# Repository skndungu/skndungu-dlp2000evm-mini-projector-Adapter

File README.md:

# skndungu-dlp2000evm-mini-projector-Adapter
dlp2000evm mini projector Raspberry Pi Adapter

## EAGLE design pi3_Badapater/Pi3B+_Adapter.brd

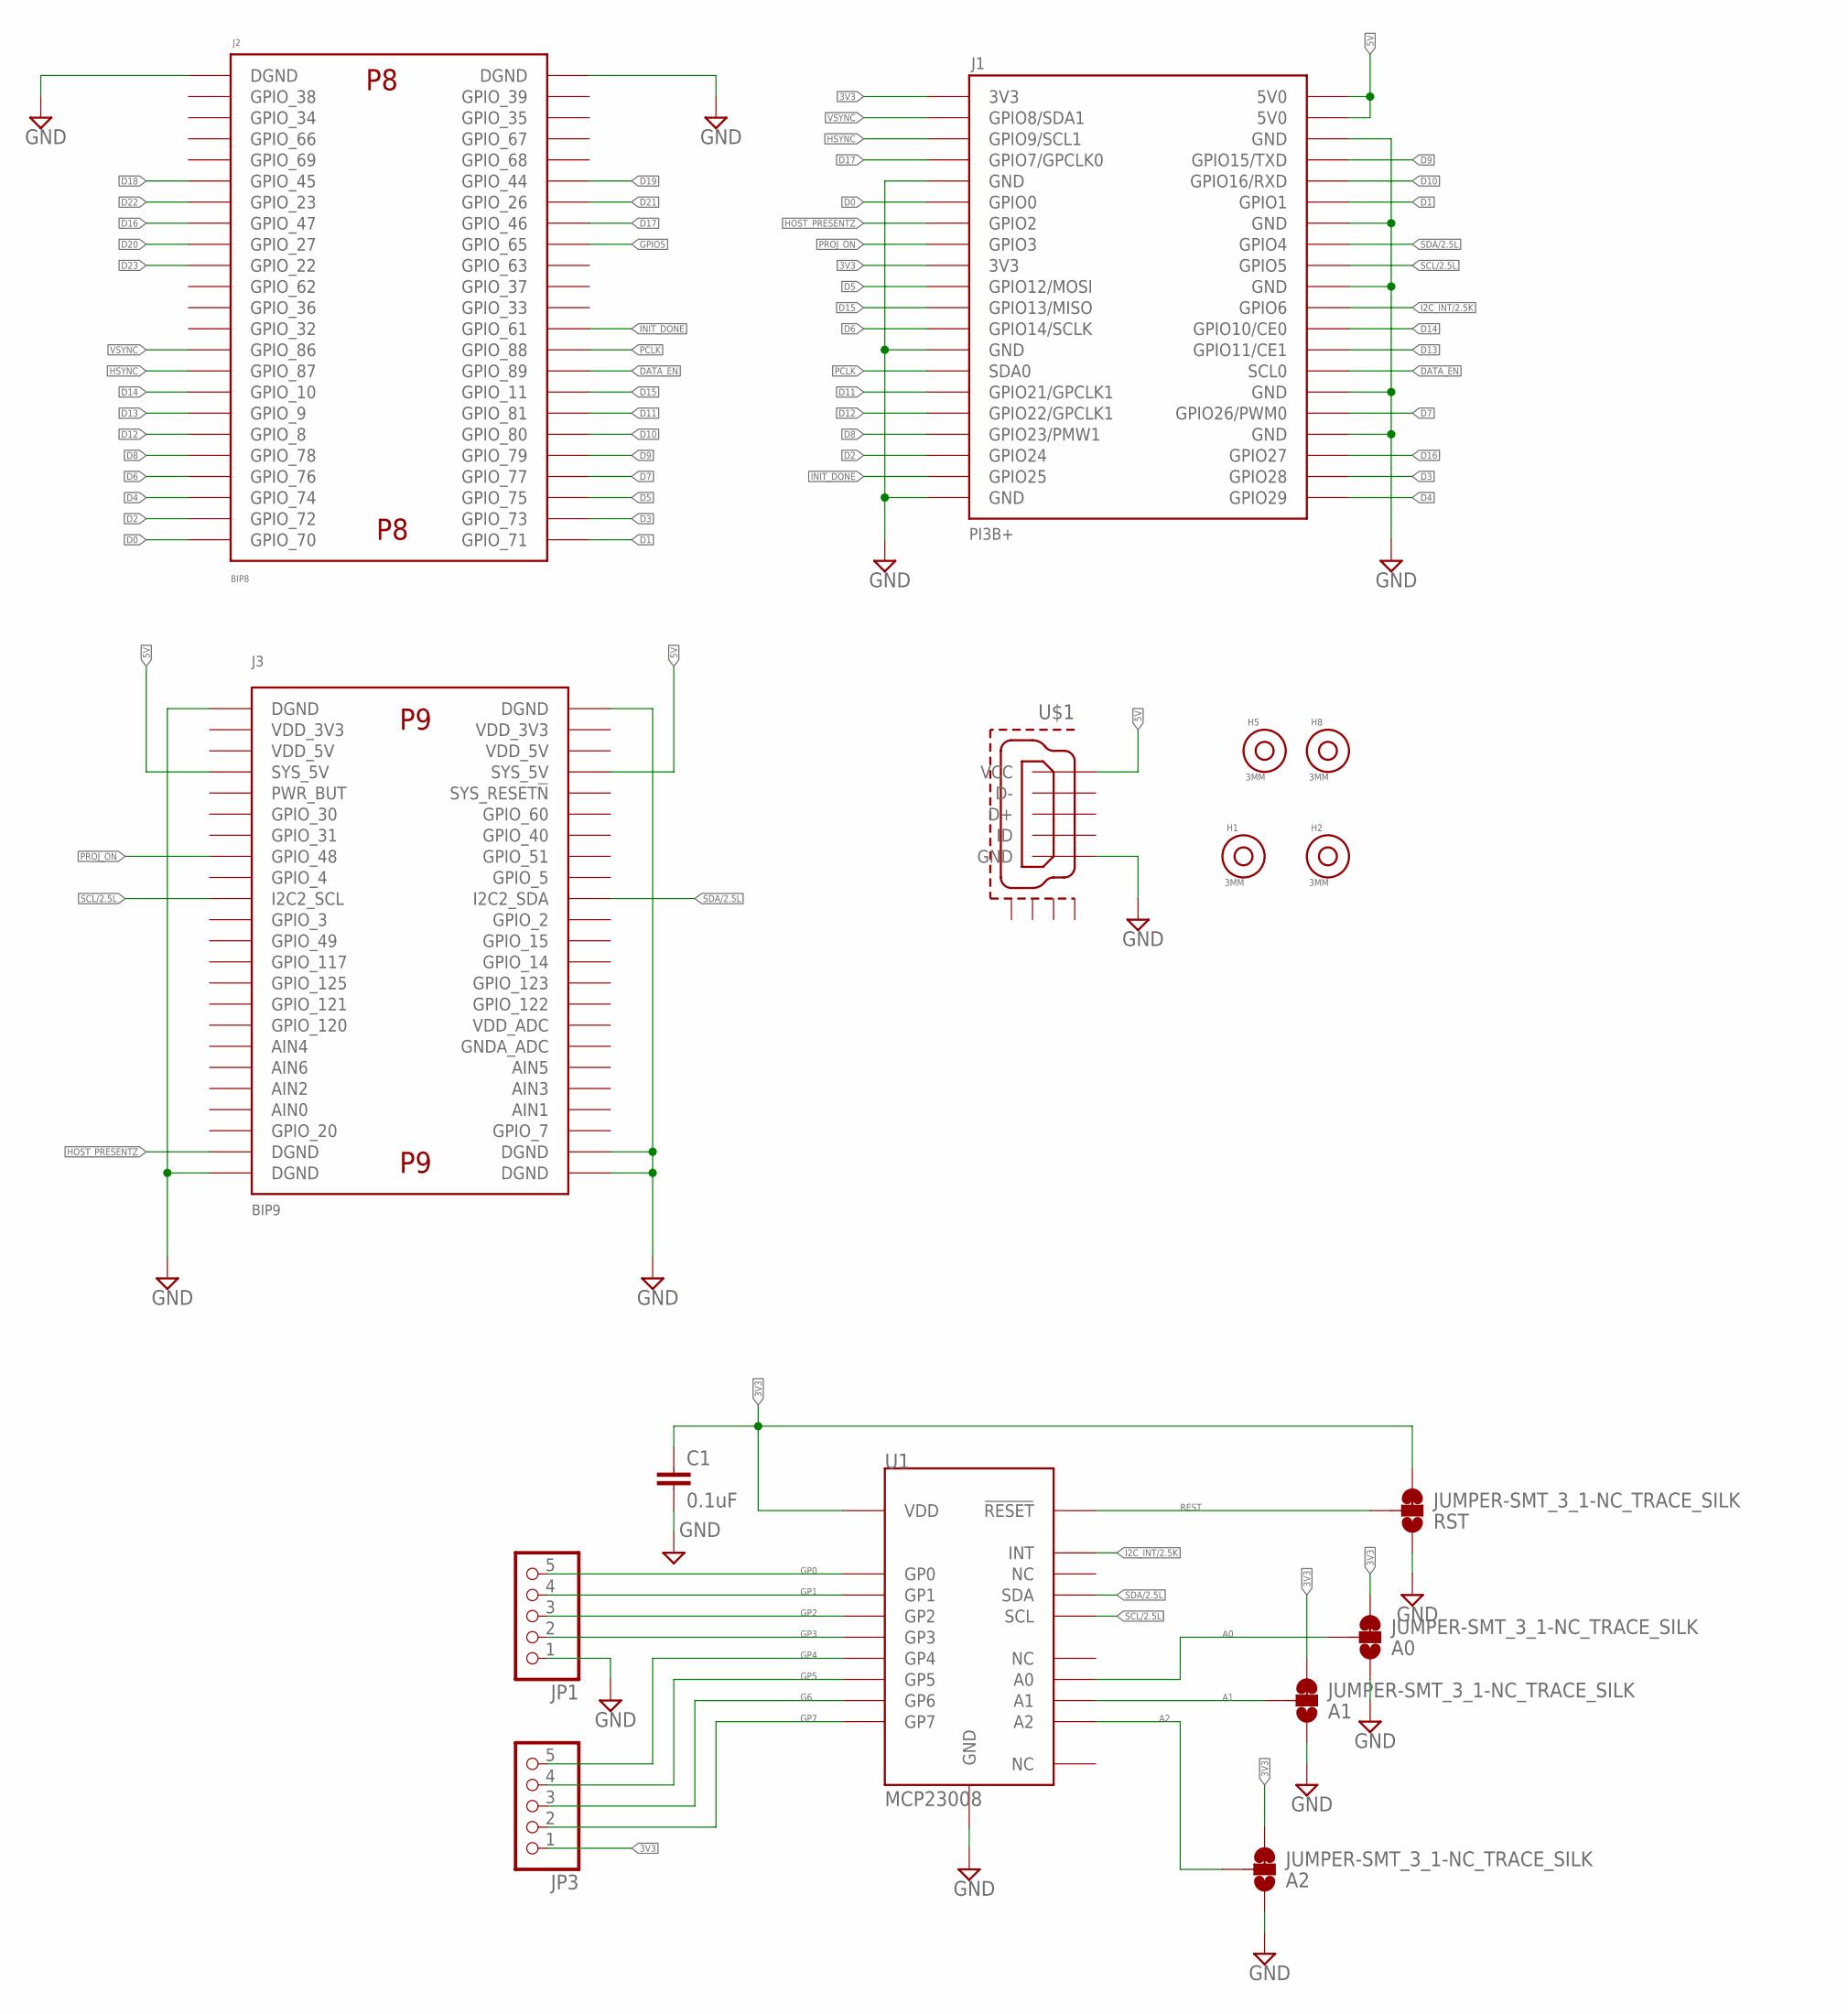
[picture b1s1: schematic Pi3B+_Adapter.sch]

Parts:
A0, A1, A2: JUMPER-SMT_3_1-NC_TRACE_SILK; SMT-JUMPER_3_1-NC_TRACE_SILK
C1: 0.1uF; 0402
H1, H2, H5, H8: 3MM
J1: PI3B+
J2: BIP8
J3: BIP9
JP1, JP3: PINHD-1X55X2MM; 1_05X2MM
RST: JUMPER-SMT_3_1-NC_TRACE_SILK; SMT-JUMPER_3_1-NC_TRACE_SILK
U1: MCP23008; MCP23008SS
U$1: MICRO-USB-RECEPTACLE47589-0001; 47589-0001

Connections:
3V3: A0.3, A1.3, A2.3, C1.1, J1.3V3, J1.3V3@1 (3V3), JP3.1, RST.3, U1.VDD
5V: J1.5V0, J1.5V0@1 (5V0), J3.SYS_5V, J3.SYS_5V@1 (SYS_5V), U$1.V-BUS (VCC)
A0: A0.2, U1.A0
A1: A1.2, U1.A1
A2: A2.2, U1.A2
D0: J1.GPIO0, J2.GPIO_70
D1: J1.GPIO1, J2.GPIO_71
D2: J1.GPIO24, J2.GPIO_72
D3: J1.GPIO28, J2.GPIO_73
D4: J1.GPIO29, J2.GPIO_74
D5: J1.GPIO12/MOSI, J2.GPIO_75
D6: J1.GPIO14/SCLK, J2.GPIO_76
D7: J1.GPIO26/PMW0 (GPIO26/PWM0), J2.GPIO_77
D8: J1.GPIO23/PWM1 (GPIO23/PMW1), J2.GPIO_78
D9: J1.GPIO15/TXD, J2.GPIO_79
D10: J1.GPIO16/RXD, J2.GPIO_80
D11: J1.GPIO21/GPCLK1, J2.GPIO_81
D12: J1.GPIO22/GPCLK2 (GPIO22/GPCLK1), J2.GPIO_8
D13: J1.GPIO11/CE1, J2.GPIO_9
D14: J1.GPIO10/CE0, J2.GPIO_10
D15: J1.GPIO13/MISO, J2.GPIO_11
D16: J1.GPIO27, J2.GPIO_47
D17: J1.GPIO7/GPCLK0, J2.GPIO_46
D18: J2.GPIO_45
D19: J2.GPIO_44
D20: J2.GPIO_27
D21: J2.GPIO_26
D22: J2.GPIO_23
D23: J2.GPIO_22
DATA_EN: J1.SCL0, J2.GPIO_89
G6: JP3.3, U1.GP6
GND: A0.1, A1.1, A2.1, C1.2, J1.GND, J1.GND@1 (GND), J1.GND@2 (GND), J1.GND@3 (GND), J1.GND@4 (GND), J1.GND@5 (GND), J1.GND@6 (GND), J1.GND@7 (GND), J2.DGND, J2.DGND@1 (DGND), J3.DGND, J3.DGND@1 (DGND), J3.DGND@4 (DGND), J3.DGND@5 (DGND), J3.DGND@6 (DGND), JP1.1, RST.1, U1.GND, U$1.GND
GP0: JP1.5, U1.GP0
GP1: JP1.4, U1.GP1
GP2: JP1.3, U1.GP2
GP3: JP1.2, U1.GP3
GP4: JP3.5, U1.GP4
GP5: JP3.4, U1.GP5
GP7: JP3.2, U1.GP7
GPIO5: J2.GPIO_65
HOST_PRESENTZ: J1.GPIO2, J3.DGND@3 (DGND)
HSYNC: J1.GPIO9/SCL1, J2.GPIO_87
I2C_INT/2.5K: J1.GPIO6, U1.INT
INIT_DONE: J1.GPIO25, J2.GPIO_61
PCLK: J1.SDA0, J2.GPIO_88
PROJ_ON: J1.GPIO3, J3.GPIO_48
REST: RST.2, U1.!RESET
SCL/2.5L: J1.GPIO5, J3.I2C2_SCL, U1.SCL
SDA/2.5L: J1.GPIO4, J3.I2C2_SDA, U1.SDA
VSYNC: J1.GPIO8/SDA1, J2.GPIO_86

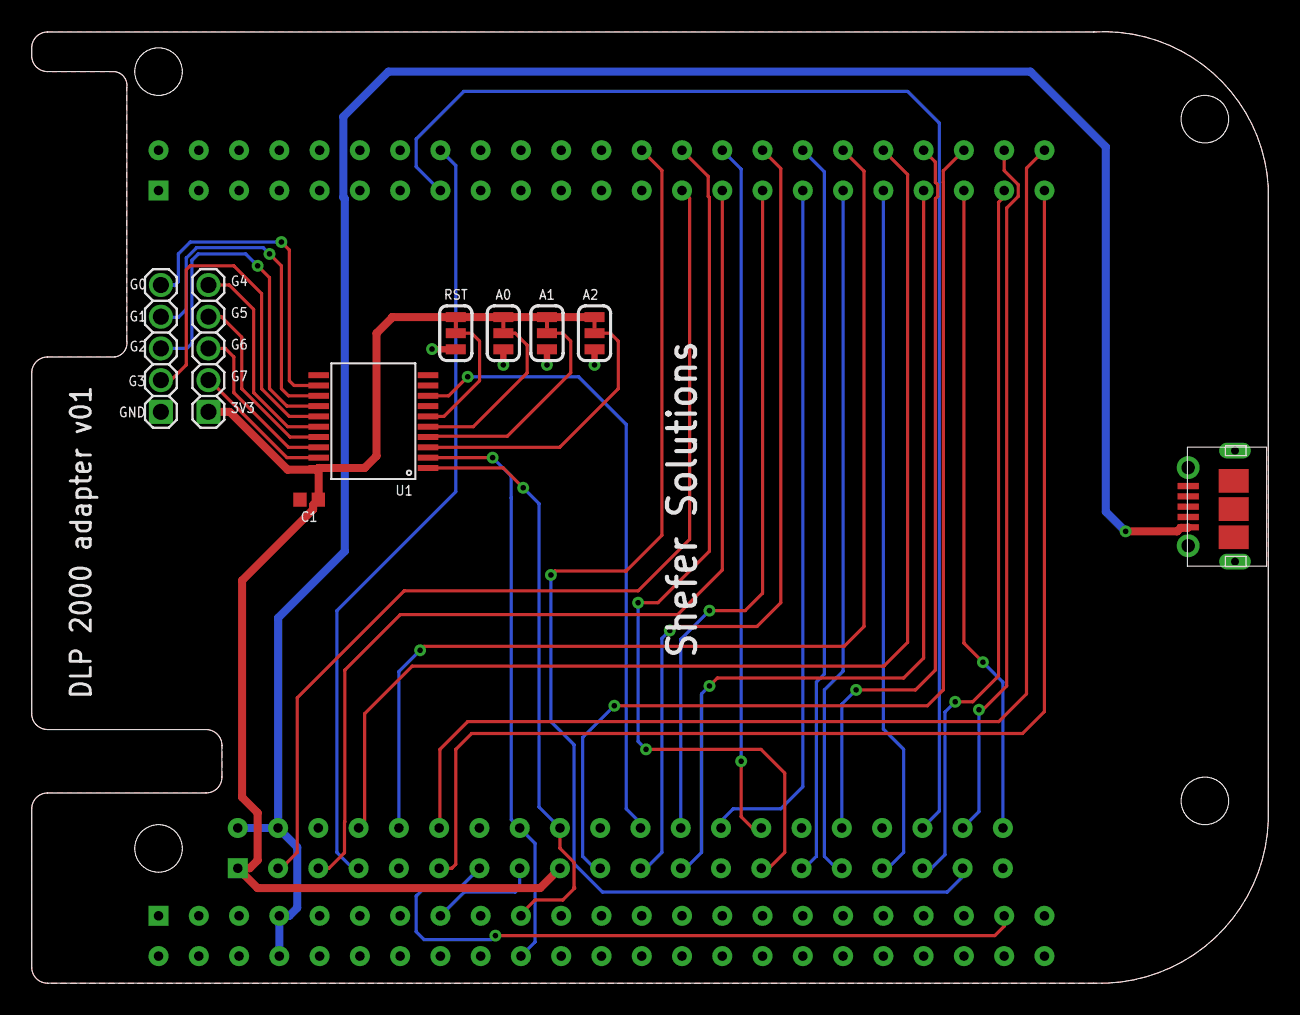
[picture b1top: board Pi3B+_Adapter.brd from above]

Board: 2 copper layers, 78.0 x 60.0 mm, 16 parts (1 on the bottom side), 43 nets.

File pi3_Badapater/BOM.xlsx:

Designator | Value | Footprint | Description | Mfr#
C1 | 0.1uF | 402 | 0.1¬µF ceramic
J1 | PI3B+ | 20 Position | Pin headers Female 2x20 2.54mm
J2 | BIP8 | 23 Position, 2.54 mm | Pin headers Female 2x23 2.54mm
J3 | BIP9 | 23 Position, 2.54 mm | Pin headers Female 2x23 2.54mm
JP1 | JP1 | 5 Position | PIN HEADER Male 5 Position 2.54mm
JP3 | JP3 | 5 position | PIN HEADER male 5 position 2.54mm
U$1 | 47589-0001 | 47589-0001 | MICRO USB RECEP | 47589-0001
U1 | MCP23008 | MCP23008SS | MCP23008SS | MCP23008SS

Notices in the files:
parts and their libraries:
con-molex-usb: (C) 2014 Tomasz Boleslaw CEDRO, cederom@tlen.pl, http://www.tomek.cedro.info.
SparkFun-Capacitors: Licensing: Creative Commons ShareAlike 4.0 International - https://creativecommons.org/licenses/by-sa/4.0
